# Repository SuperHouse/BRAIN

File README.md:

Building Brain Home Automation Controller
==========================================
Copyright 2016-2018 SuperHouse Automation Pty Ltd  www.superhouse.tv  

Home automation controller based on a Raspberry Pi. A Raspberry Pi 3
attaches to this board, which is Arduino-compatible (ATmega328P) and
includes a switch-mode power supply for the Pi, plus 433MHz transmitter
and receiver modules connected to the Arduino. The Arduino can
communicate with the Pi via serial using onboard 3.3V/5V level
shifters, and can send / receive RF messages using the 433MHz modules.

Features:

 * ATmega328P MCU
 * 5V switchmode power supply
 * 433MHz transmitter
 * 433MHz receiver
 * Status LEDs

INSTALLATION
------------
The design is saved as an EAGLE project. EAGLE PCB design software is
available from www.cadsoftusa.com free for non-commercial use. To use
this project download it and place the directory containing these files
into the "eagle" directory on your computer. Then open EAGLE and
navigate to the project.

CREDITS
-------
Designed by Jonathan Oxer jon@oxer.com.au

DISTRIBUTION
------------
The specific terms of distribution of this project are governed by the
license referenced below.

LICENSE
-------
Licensed under the TAPR Open Hardware License (www.tapr.org/OHL).
The "license" folder within this repository also contains a copy of
this license in plain text format.

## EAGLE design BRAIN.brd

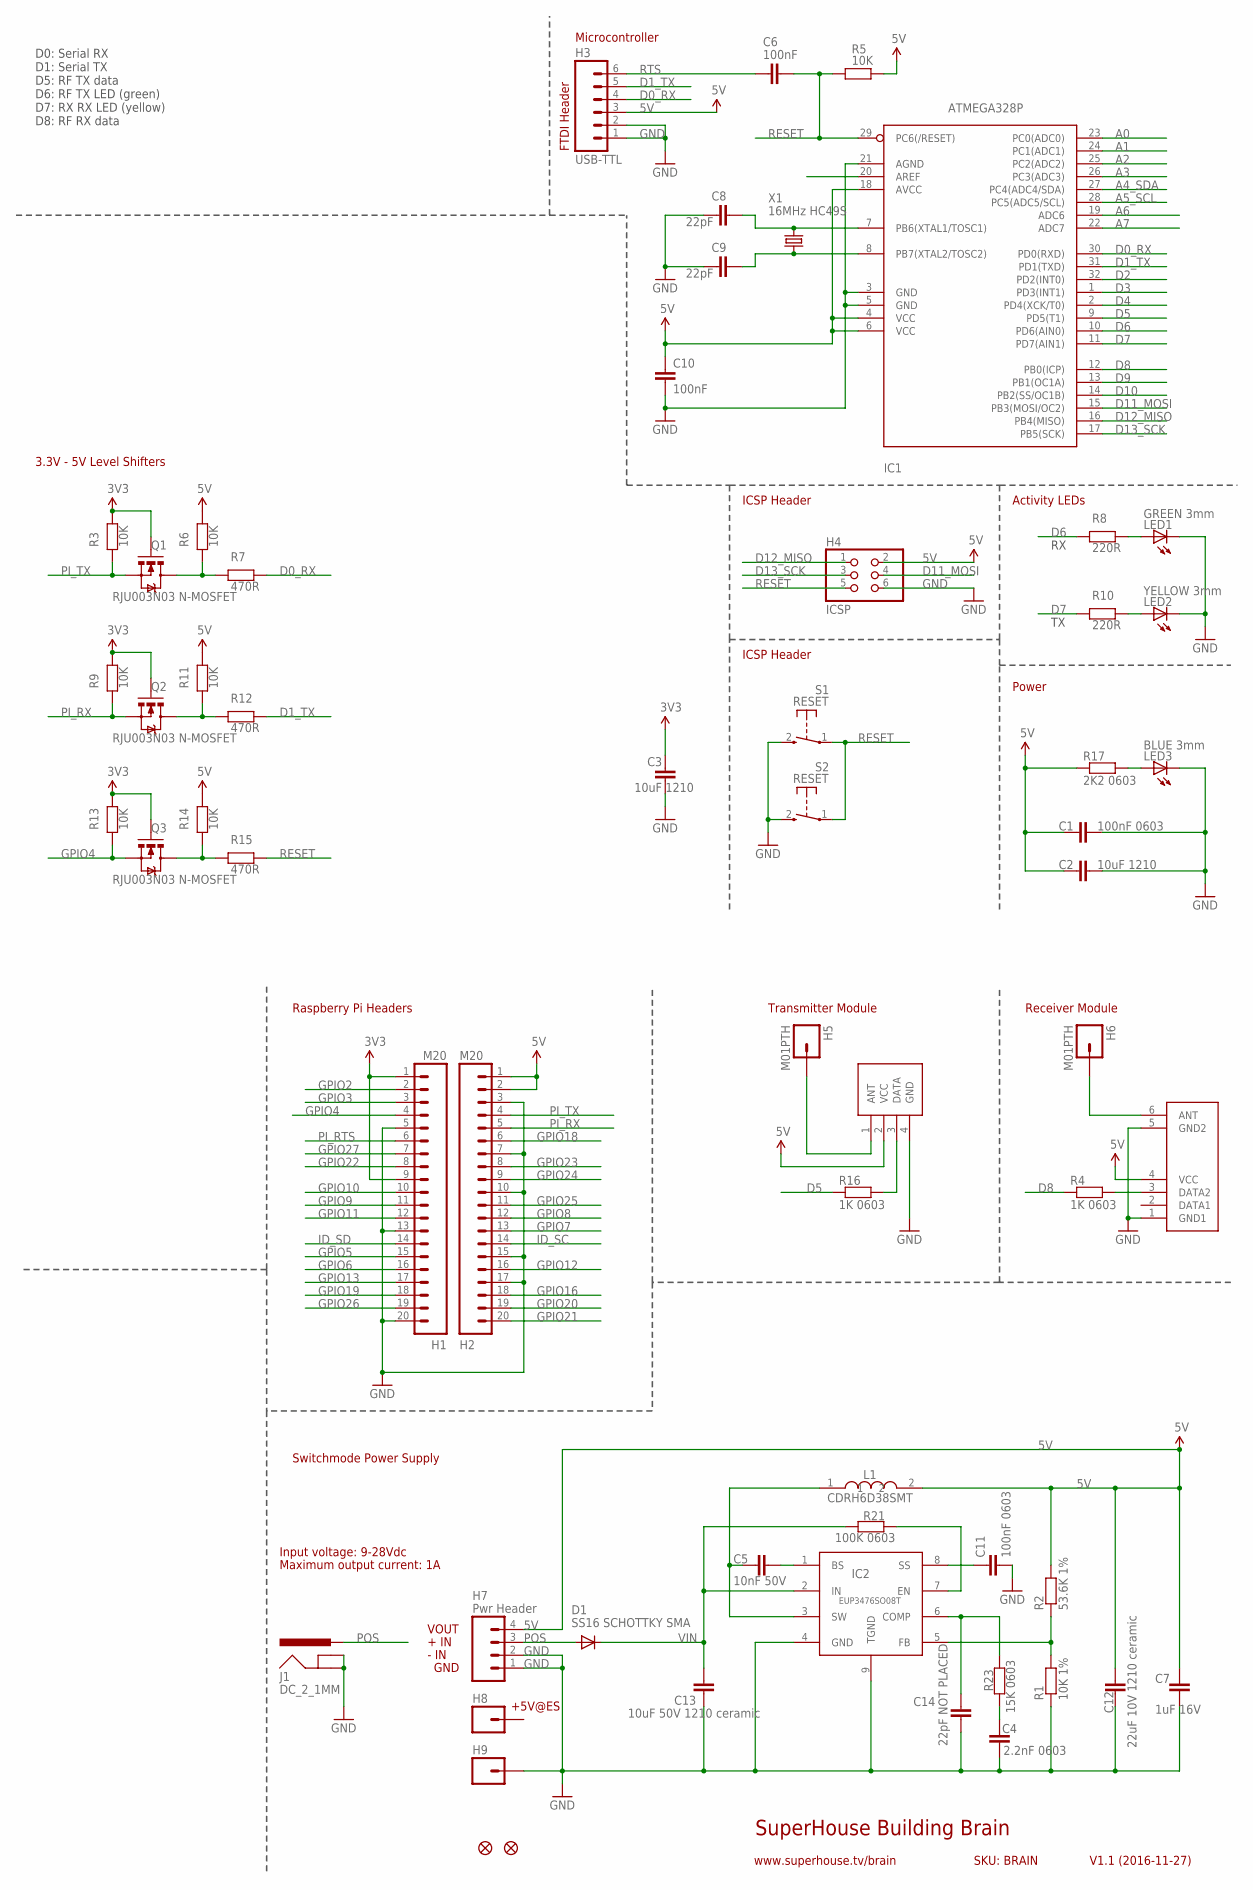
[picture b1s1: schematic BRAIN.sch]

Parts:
C1, C11: 100nF 0603; 0603
C2, C3: 10uF 1210; C1210
C4: 2.2nF 0603; 0603
C5: 10nF 50V; 0603
C6, C10: 100nF; 0603
C7: 1uF 16V; 0603
C8, C9: 22pF; 0603
C12: 22uF 10V 1210 ceramic; C1210
C13: 10uF 50V 1210 ceramic; C1210
C14: 22pF NOT PLACED; 0603
D1: SS16 SCHOTTKY SMA; SMA-SMB-DIODE
H1, H2: M20; 1X20
H3: USB-TTL; 1X06
H4: ICSP; 2X03
H5, H6, H8, H9: M01PTH; 1X01
H7: Pwr Header; 1X04
IC1: ATMEGA328P; TQFP32-08
IC2: EUP3476SO08T; SO08T
IC3: RXB1; RX-B1-SHORT-FLAT
IC4: TX-C1FLAT; TX-C1-FLAT
J1: DC_2_1MM; POWER_JACK_PTH
L1: CDRH6D38SMT; CDRH
LED1: GREEN 3mm; LED3MM
LED2: YELLOW 3mm; LED3MM
LED3: BLUE 3mm; LED3MM
Q1, Q2, Q3: RJU003N03 N-MOSFET; SOT32-3
R1: 10K 1%; 0603
R2: 53.6K 1%; 0603
R3, R5, R6, R9, R11, R13, R14: 10K; 0603
R4, R16: 1K 0603; 0603
R7, R12, R15: 470R; 0603
R8, R10: 220R; 0603
R17: 2K2 0603; 0603
R21: 100K 0603; 0603
R23: 15K 0603; 0603
S1, S2: RESET; TACTILE_SWITCH_SMD_2PIN_TINY
U$4, U$5: FIDUCIAL1X2.5; FIDUCIAL-1X2.5
X1: 16MHz HC49S; HC49U-V

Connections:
3.3V: C3.1, H1.1, H1.9, Q1.1 (G), Q2.1 (G), Q3.1 (G), R3.1, R9.1, R13.1
5V: C1.1, C2.2, C7.1, C10.1, C12.1, H2.1, H2.2, H3.3, H4.2, H7.4, IC1.4 (VCC), IC1.6 (VCC), IC1.18 (AVCC), IC3.4 (VCC), IC4.2 (VCC), L1.2, R2.2, R5.2, R6.1, R11.1, R14.1, R17.1
A0: IC1.23 (PC0(ADC0))
A1: IC1.24 (PC1(ADC1))
A2: IC1.25 (PC2(ADC2))
A3: IC1.26 (PC3(ADC3))
A4_SDA: IC1.27 (PC4(ADC4/SDA))
A5_SCL: IC1.28 (PC5(ADC5/SCL))
A6: IC1.19 (ADC6)
A7: IC1.22 (ADC7)
AREF: IC1.20 (AREF)
D0_RX: H3.4, IC1.30 (PD0(RXD)), R7.1
D1_TX: H3.5, IC1.31 (PD1(TXD)), R12.1
D2: IC1.32 (PD2(INT0))
D3: IC1.1 (PD3(INT1))
D4: IC1.2 (PD4(XCK/T0))
D5: IC1.9 (PD5(T1)), R16.1
D6: IC1.10 (PD6(AIN0)), R8.2
D7: IC1.11 (PD7(AIN1)), R10.2
D8: IC1.12 (PB0(ICP)), R4.1
D9: IC1.13 (PB1(OC1A))
D10: IC1.14 (PB2(SS/OC1B))
D11_MOSI: H4.4, IC1.15 (PB3(MOSI/OC2))
D12_MISO: H4.1, IC1.16 (PB4(MISO))
D13_SCK: H4.3, IC1.17 (PB5(SCK))
GND: C1.2, C2.1, C3.2, C4.2, C7.2, C8.1, C9.1, C10.2, C11.2, C12.2, C13.2, C14.2, H1.5, H1.13, H1.20, H2.3, H2.7, H2.10, H2.15, H2.17, H3.1, H3.2, H4.6, H7.1, H7.2, H9.1, IC1.3 (GND), IC1.5 (GND), IC1.21 (AGND), IC2.4 (GND), IC2.9 (TGND), IC3.1 (GND1), IC3.5 (GND2), IC4.4 (GND), J1.GND, J1.GNDBREAK, LED1.K (C), LED2.K (C), LED3.K (C), R1.1, S1.2 (S), S2.2 (S)
GPIO2: H1.2
GPIO3: H1.3
GPIO4: H1.4, Q3.2 (S), R13.2
GPIO5: H1.15
GPIO6: H1.16
GPIO7: H2.13
GPIO8: H2.12
GPIO9: H1.11
GPIO10: H1.10
GPIO11: H1.12
GPIO12: H2.16
GPIO13: H1.17
GPIO16: H2.18
GPIO18: H2.6
GPIO19: H1.18
GPIO20: H2.19
GPIO21: H2.20
GPIO22: H1.8
GPIO23: H2.8
GPIO24: H2.9
GPIO25: H2.11
GPIO26: H1.19
GPIO27: H1.7
ID_SC: H2.14
ID_SD: H1.14
unnamed: LED3.A, R17.2
unnamed: Q1.3 (D), R6.2, R7.2
unnamed: H6.1, IC3.6 (ANT)
unnamed: H5.1, IC4.1 (ANT)
unnamed: C8.2, IC1.7 (PB6(XTAL1/TOSC1)), X1.2
unnamed: IC4.3 (DATA), R16.2
unnamed: Q2.3 (D), R11.2, R12.2
unnamed: Q3.3 (D), R14.2, R15.2
unnamed: IC2.7 (EN), R21.1
unnamed: IC2.5 (FB), R1.2, R2.1
unnamed: C14.1, IC2.6 (COMP), R23.2
unnamed: C11.1, IC2.8 (SS)
unnamed: C9.2, IC1.8 (PB7(XTAL2/TOSC2)), X1.1
unnamed: LED1.A, R8.1
unnamed: LED2.A, R10.1
unnamed: C5.2, IC2.1 (BS)
unnamed: C5.1, IC2.3 (SW), L1.1
unnamed: IC3.3 (DATA2), R4.2
unnamed: C4.1, R23.1
PI_RTS: H1.6
PI_RX: H2.5, Q2.2 (S), R9.2
PI_TX: H2.4, Q1.2 (S), R3.2
POS: D1.A, H7.3, J1.PWR
RESET: C6.2, H4.5, IC1.29 (PC6(/RESET)), R5.1, R15.1, S1.1, S2.1
RTS: C6.1, H3.6
VIN: C13.1, D1.C, IC2.2 (IN), R21.2

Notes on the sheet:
SuperHouse Building Brain
SKU: BRAIN
V1.1 (2016-11-27)
Power
Receiver Module
www.superhouse.tv/brain
D0: Serial RX D1: Serial TX D5: RF TX data D6: RF TX LED (green) D7: RX RX LED (yellow) D8: RF RX data
ICSP Header
Microcontroller
FTDI Header
VOUT
+ IN
- IN
GND
Input voltage: 9-28Vdc
Maximum output current: 1A
+5V@ES
Transmitter Module
Raspberry Pi Headers
Switchmode Power Supply
3.3V - 5V Level Shifters
Activity LEDs

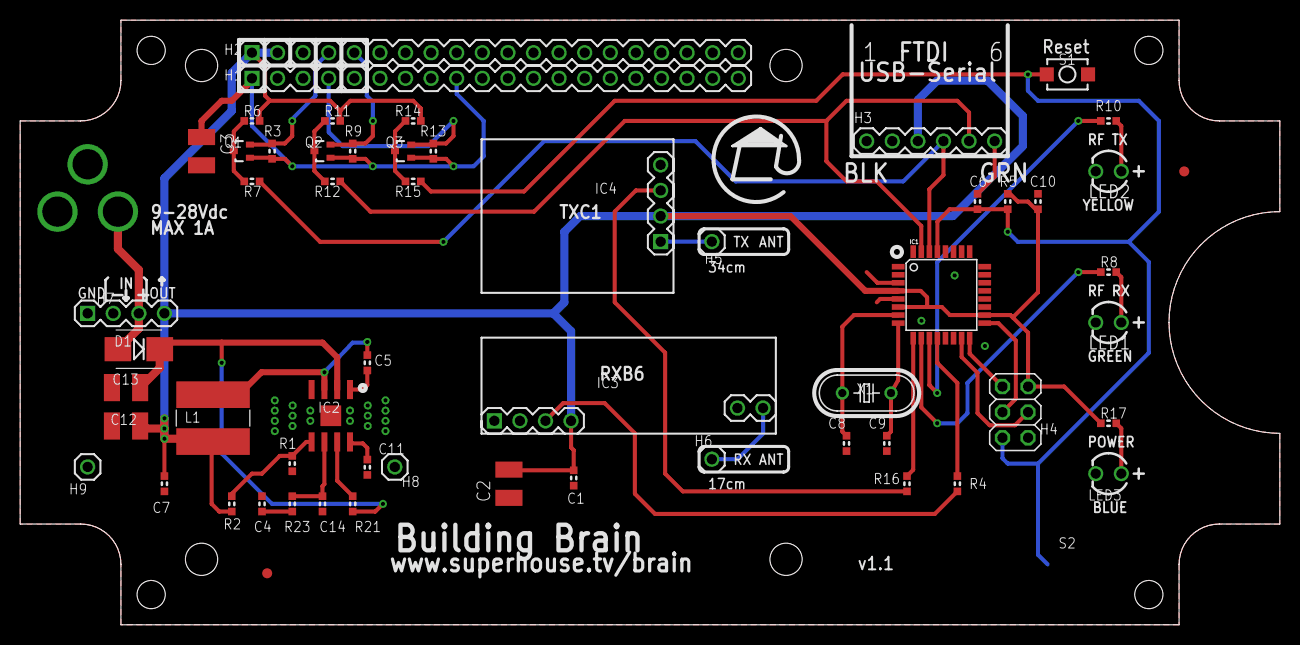
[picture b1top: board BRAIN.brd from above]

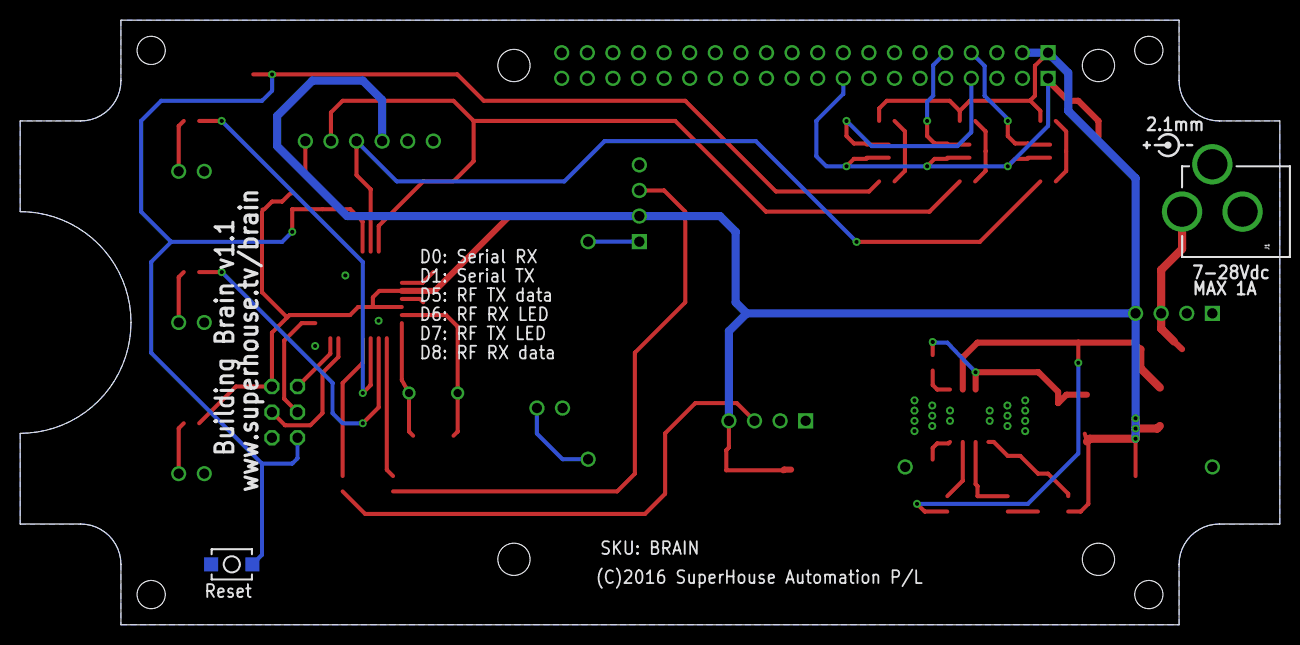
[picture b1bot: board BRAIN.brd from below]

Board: 2 copper layers, 125.0 x 60.0 mm, 60 parts (2 on the bottom side), 38 nets.

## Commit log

2016-11-27 Initial project import
2016-11-27 Moved Arduino RESET line from RTS to GPIO4 for manual control
2016-11-27 Replaced 0805 footprints with 1210
2016-11-27 Increased Pi holes to 3.2mm and marked Pi headers in use
2016-11-27 Fixed version on silkscreen
2018-03-23 Improved designators
2018-03-23 Renamed project files and added documentation
2018-03-23 Named files back again to match the SKU

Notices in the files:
BRAIN.brd:
(C)2016 SuperHouse Automation P/L
